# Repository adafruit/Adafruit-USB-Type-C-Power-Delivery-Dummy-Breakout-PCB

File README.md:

## Adafruit USB Type C Power Delivery Dummy Breakout - I2C or Fixed - HUSB238 PCB

<a href="http://www.adafruit.com/products/5807"><br/>
Click here to purchase one from the Adafruit shop</a>

PCB files for the Adafruit USB Type C Power Delivery Dummy Breakout - I2C or Fixed - HUSB238. 

Format is EagleCAD schematic and board layout
* https://www.adafruit.com/product/5807

### Description

The HUSB238 USB PD sink chip is neat in that you can either use jumpers (really, resistor selection) to set the desired PD voltage and current or you can use I2C for dynamic querying and setting. We've build a nice Adafruit USB Type C Power Delivery Dummy Breakout board around the HUSB238 to make it very easy to configure and integrate without having to solder any tiny resistors.

It's perfect for use with USB Type C wall adapters that can provide multiple voltages, the standard offerings are 5V, 9V, 12V, 15V, 18V and 20V. This HUSB238 breakout plugs into the USB C cable and then over the CC lines will negotiate the PD request and commands. For example we can ask what voltages are available and then pick the highest one. Or if you need a specific voltage it will specifically select that one.

This breakout will be handy for projects where you need a lot more than 5V @ 2A power: this adapter can give up to 20V at 5A - yes you can get 100W over USB C! - and you could buck that down to get a ton of current at 5V or 12V if that's needed. Or use it to convert a DC or battery-powered device into a USB C powered one!

Jumper-configured usage is simple: by default its hard-wired for 5V 1A output since that's what USB C will always provide at first. Cut the 5V jumper and solder closed the 9V, 12V, 15V, 18V or 20V jumper to select the resistor that sets the voltage. You can also select the desired current from 2A to 3A, although we have found that this isn't as essential, you could always just pull as much as the adapter will provide. No microcontroller or microcomputer is required!

I2C-configured usage is a little more challenging. Since the Vout can be as high as 20V we don't have an onboard voltage regulator or pullup resistors. Connect to a microcontroller or microcomputer board that has a separate power supply (or that can regulate from up-to-20V if you plan on selecting that high) and I2C pullup resistors to your desired logic level. Then use the Arduino library and example code to query the USB Type C PD source for available voltages and currents and select the desired voltage dynamically. When configuring over I2C, the jumper settings are used on startup until the I2C commands come over.

Comes with a small bit of header and a terminal block so you can decide whether you want to use it in a breadboard, or free-wired.

### License

Adafruit invests time and resources providing this open source design, please support Adafruit and open-source hardware by purchasing products from [Adafruit](https://www.adafruit.com)!

Designed by Limor Fried/Ladyada for Adafruit Industries.

Creative Commons Attribution/Share-Alike, all text above must be included in any redistribution. 
See license.txt for additional details.

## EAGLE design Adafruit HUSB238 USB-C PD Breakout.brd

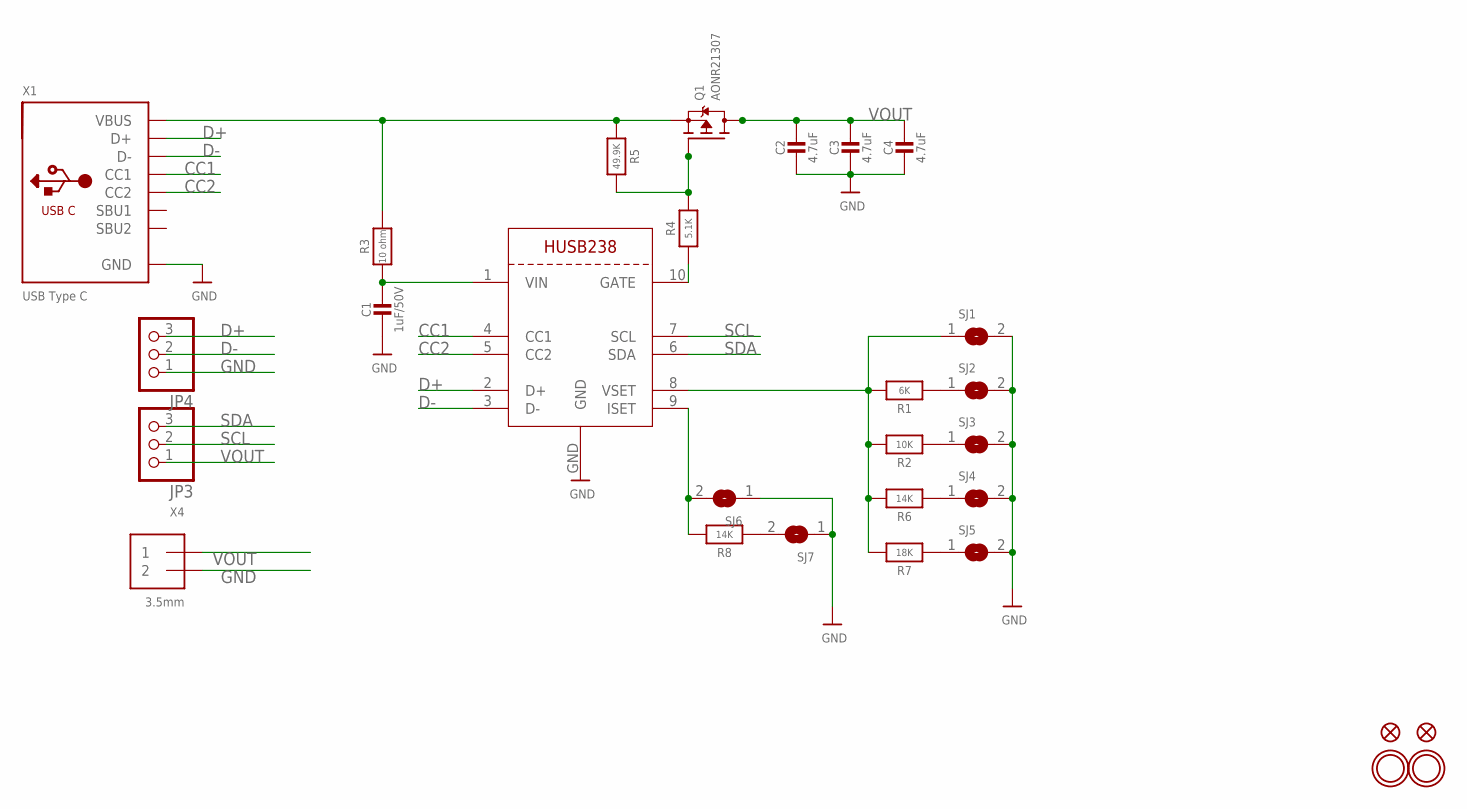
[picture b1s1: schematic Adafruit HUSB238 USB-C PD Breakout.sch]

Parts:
C1: 1uF/50V; 0805-NO
C2, C3, C4: 4.7uF; 0805-NO
FID1, FID2: FIDUCIAL_1MM
JP3, JP4: HEADER-1X3ROUND; 1X03_ROUND
Q1: AONR21307; POWERDI3333
R1: 6K; 0603-NO
R2: 10K; 0603-NO
R3: 10 ohm; 0603-NO
R4: 5.1K; 0603-NO
R5: 49.9K; 0603-NO
R6, R8: 14K; 0603-NO
R7: 18K; 0603-NO
SJ1, SJ6: SOLDERJUMPERCLOSED; SOLDERJUMPER_CLOSEDWIRE
SJ2, SJ3, SJ4, SJ5, SJ7: SOLDERJUMPER; SOLDERJUMPER_ARROW_NOPASTE
U$1, U$2: MOUNTINGHOLE2.5; MOUNTINGHOLE_2.5_PLATED
X1: USB Type C; USB_C_CUSB31-CFM2AX-01-X
X3: HUSB238; DFN10_3X3MM
X4: 3.5mm; TERMBLOCK_1X2-3.5MM

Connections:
CC1: X1.A5 (CC1), X3.4 (CC1)
CC2: X1.B5 (CC2), X3.5 (CC2)
D+: JP4.3, X1.A6 (D+), X1.B6 (D+), X3.2 (D+)
D-: JP4.2, X1.A7 (D-), X1.B7 (D-), X3.3 (D-)
GND: C1.2, C2.2, C3.2, C4.2, JP4.1, SJ1.2, SJ2.2, SJ3.2, SJ4.2, SJ5.2, SJ6.1, SJ7.1, X1.A1B12 (GND), X1.B1A12 (GND), X3.GND, X4.2
unnamed: C1.1, R3.1, X3.1 (VIN)
unnamed: Q1.4 (G), R4.2, R5.2
unnamed: R1.2, R2.2, R6.2, R7.2, SJ1.1, X3.8 (VSET)
unnamed: R4.1, X3.10 (GATE)
unnamed: R1.1, SJ2.1
unnamed: R2.1, SJ3.1
unnamed: R6.1, SJ4.1
unnamed: R7.1, SJ5.1
unnamed: R8.2, SJ6.2, X3.9 (ISET)
unnamed: R8.1, SJ7.2
SCL: JP3.2, X3.7 (SCL)
SDA: JP3.3, X3.6 (SDA)
VBUS: Q1.1 (S), Q1.2 (S), Q1.3 (S), R3.2, R5.1, X1.A4B9 (VBUS), X1.B4A9 (VBUS)
VOUT: C2.1, C3.1, C4.1, JP3.1, Q1.5678 (D), X4.1

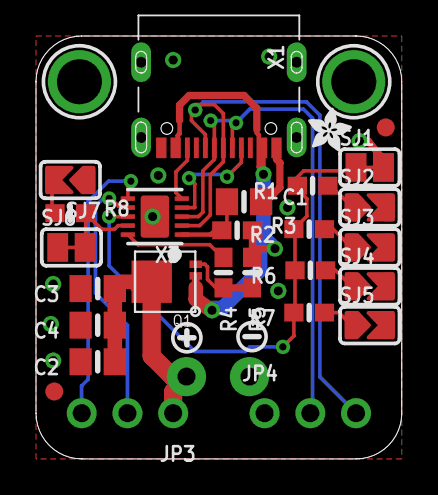
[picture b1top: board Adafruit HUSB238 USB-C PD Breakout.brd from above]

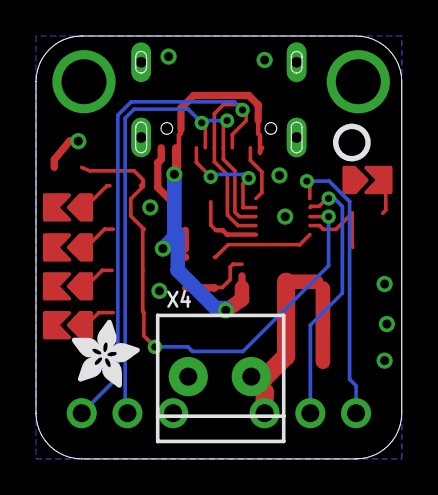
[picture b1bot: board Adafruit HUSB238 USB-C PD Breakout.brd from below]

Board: 2 copper layers, 20.3 x 23.5 mm, 54 parts (5 on the bottom side), 19 nets.

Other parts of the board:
PLABEL0: PLABEL0
PLABEL1: PLABEL1
PLABEL2: PLABEL2
PLABEL3: PLABEL3
PLABEL4: PLABEL4
PLABEL5: PLABEL5
PLABEL6: PLABEL6
PLABEL7: PLABEL7
PLABEL8: PLABEL8
PLABEL9: PLABEL9
PLABEL10: PLABEL10
PLABEL11: PLABEL11
PLABEL12: PLABEL12
PLABEL13: PLABEL13
PLABEL14: PLABEL14
PLABEL15: PLABEL15
PLABEL16: PLABEL16
PLABEL17: PLABEL17
PLABEL18: PLABEL18
PLABEL19: PLABEL19
U$3: ADAFRUIT_2.5MM
U$7: SYMBOL_PLUS
U$8: PCBFEAT-REV-040
U$9: ADAFRUIT_3.5MM
U$14: SYMBOL_MINUS

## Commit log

2023-09-25 adding cookiecutter output

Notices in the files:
parts and their libraries:
microbuilder: This work is placed in the public domain, and may be freely used for commercial and non-commercial work with the following conditions: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
